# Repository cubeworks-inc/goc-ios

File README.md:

GOC Interface App for iOS
=========================

This app allows you to use your phone to send messages to M3 chips via the GOC
protocol using an iOS device.

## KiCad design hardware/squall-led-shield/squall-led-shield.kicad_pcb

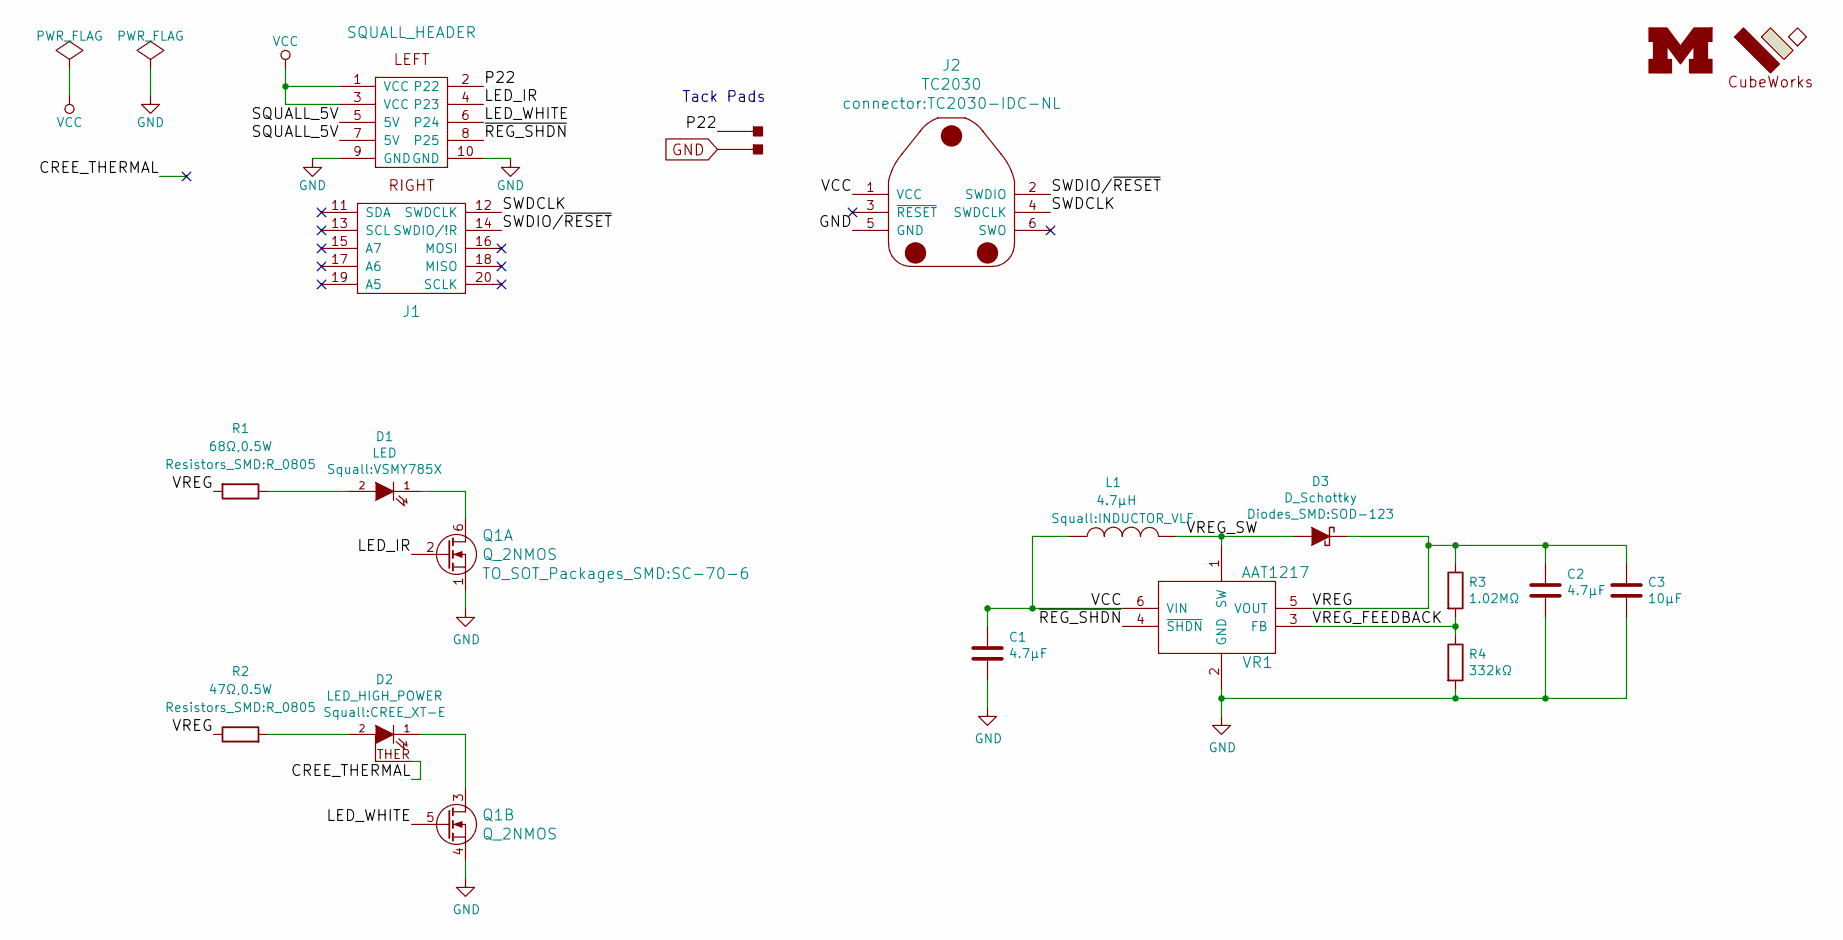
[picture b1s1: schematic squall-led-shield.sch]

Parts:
C1, C2: 4.7µF; C_0603
C3: 10µF; C_0603
D1: LED; VSMY785X
D2: LED_HIGH_POWER; CREE_XT-E
D3: D_Schottky; SOD-123
J1: SQUALL_HEADER
J2: TC2030; TC2030-IDC-NL
J3, J4: TACK_PAD; TACK_PAD_FB_75MIL
L1: 4.7µH; INDUCTOR_VLF
Q1: Q_2NMOS; SC-70-6
R1: 68Ω,0.5W; R_0805
R2: 47Ω,0.5W; R_0805
R3: 1.02MΩ; R_0603
R4: 332kΩ; R_0603
VR1: AAT1217; SOT-23-6
_1: CubeWorks-Logo; CubeWorks_Logo-5mm
_2: BLOCK_M; BLOCK_M_SOLID_100MIL

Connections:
/CREE_THERMAL: D2.THER (THERMAL)
/LED_IR: J1.4 (P23), Q1.2 (G1)
/LED_WHITE: J1.6 (P24), Q1.5 (G2)
/P22: J1.2 (P22), J3.1
/SQUALL_5V: J1.5 (5V), J1.7 (5V)
/SWDCLK: J1.12 (SWDCLK), J2.4 (SWDCLK)
/SWDIO/~RESET: J1.14 (SWDIO/!R), J2.2 (SWDIO)
/VREG: C2.1, C3.1, D3.1 (K), R1.2, R2.1, R3.1, VR1.5 (VOUT)
/VREG_FEEDBACK: R3.2, R4.1, VR1.3 (FB)
/VREG_SW: D3.2 (A), L1.2, VR1.1 (SW)
/~REG_SHDN: J1.8 (P25), VR1.4 (~SHDN)
GND: C1.2, C2.2, C3.2, J1.9 (GND), J1.10 (GND), J2.5 (GND), J4.1, Q1.1 (S1), Q1.4 (S1), R4.2, VR1.2 (GND)
unnamed: D1.1 (K), Q1.6 (D1)
unnamed: D1.2 (A), R1.1
unnamed: D2.1 (K), Q1.3 (D1)
unnamed: D2.2 (A), R2.2
VCC: C1.1, J1.1 (VCC), J1.3 (VCC), J2.1 (VCC), L1.1, VR1.6 (VIN)

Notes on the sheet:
Tack Pads

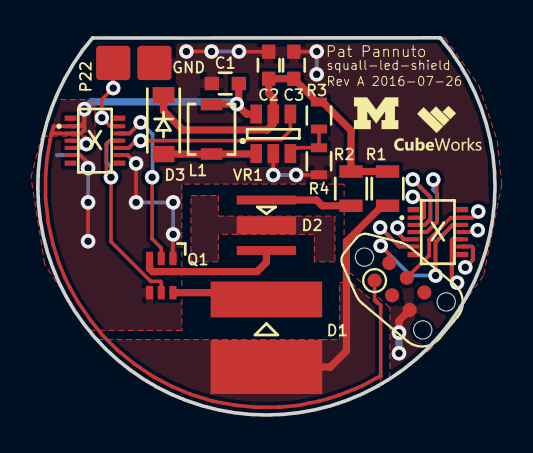
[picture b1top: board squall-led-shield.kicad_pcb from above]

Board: 2 copper layers, 25.4 x 21.0 mm, 19 parts (0 on the bottom side), 16 nets.

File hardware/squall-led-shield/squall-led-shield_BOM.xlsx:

Reference | Quantity | Value | Footprint | Datasheet | Description | Digikey | MFN | MFP
C1 C2 | 2 | 4.7µF | Capacitors_SMD:C_0603 |  |  | 490-3297-1-ND
C3 | 1 | 10µF | Capacitors_SMD:C_0603 |  |  | 490-3298-1-ND
D1 | 1 | LED | Squall:VSMY785X | http://www.vishay.com/docs/81145/vsmy7850.pdf | IR LED 850NM 1A | VSMY7850X01-GS08CT-ND | Vishay | VSMY7850X01-GS08
D2 | 1 | LED_HIGH_POWER | Squall:CREE_XT-E | http://www.cree.com/~/media/Files/Cree/LED%20Components%20an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 | LED XLAMP COOL WHITE 6200K 2SMD | XTEAWT-00-0000-000000G51CT-ND | ,
D3 | 1 | D_Schottky | Diodes_SMD:SOD-123 | http://www.onsemi.com/pub_link/Collateral/MBR0520LT1-D.PDF | DIODE SCHOTTKY 20V 500MA SOD123 | MBR0520LT1GOSCT-ND | ON Semiconductor | MBR0520LT1G
J1 | 1 | SQUALL_HEADER | Squall:SQUALL_HEADER |  | Header for a sensor board on top of the Squall BLE tag board. | H11617CT-ND | ,
L1 | 1 | 4.7µH | Squall:INDUCTOR_VLF | http://www.tdkkorea.co.kr/pro/down_pdf.php?No=75&real_file=1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 | 4.7µH Shielded Wirewound Inductor 740mA 190 mOhm Max Nonstandard | 445-3225-1-ND | TDK-Corporation | VLF3012AT-4R7MR74
Q1 | 1 | Q_2NMOS | TO_SOT_Packages_SMD:SC-70-6 | http://www.vishay.com/docs/67192/si1922ed.pdf | MOSFET 2N-CH 20V 1.3A SOT-363 | SI1922EDH-T1-GE3CT-ND | ,
R1 | 1 | 68Ω,0.5W | Resistors_SMD:R_0805 |  | RES SMD 68 OHM 5% 1/2W 0805 | P68ADCT-ND | ,
R2 | 1 | 47Ω,0.5W | Resistors_SMD:R_0805 |  | RES SMD 47 OHM 5% 1/2W 0805 | P47ADCT-ND | ,
R3 | 1 | 1.02MΩ | Resistors_SMD:R_0603 |  |  | 541-1.02MHCT-ND
R4 | 1 | 332kΩ | Resistors_SMD:R_0603 |  |  | 541-332KHCT-ND
VR1 | 1 | AAT1217 | TO_SOT_Packages_SMD:SOT-23-6 | http://www.skyworksinc.com/uploads/documents/AAT1217_202050B.pdf | Boost Switching Regulator IC Positive Adjustable 2.5V 1 Output 750mA (Switch) S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 | 863-1495-1-ND | Skyworks-Solutions-Inc. | AAT1217ICA-1.2-T1

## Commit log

2016-07-19 Initial UI
2016-07-21 Simple case GOC message generation working
2016-07-21 Add README
2016-07-21 Remove old attempts at UI interfacing
2016-07-21 Wire up GOC version; make GOCv1 work correctly
2016-07-21 Wire send buttons; fix validation logic
2016-07-21 Basic LED blinking code
    Not sure that iOS can support what we need :/, this gets a roughly
    40Hz strobe with maybe a 90% duty cycle. The Electric Imp BlinkUp
    protocol blinks the screen instead, getting a better balance, but
    they max out around 15 Hz, which given screen refresh rates isn't
    that surprising.
    Harumph.
2016-07-21 Move iPhone app into dedicated iOS folder
2016-07-21 Fix typo in userdefaults initializer
2016-07-24 WIP: Squall shield programming perhipheral
    This is my first time ever using KiCad, so likely rough.
2016-07-24 Put Squall headers on both sides of the board
2016-07-24 Not sure I agree that netlist file shouldn't be committed
2016-07-24 Add missing footprint for R2
2016-07-24 WIP: Place parts
2016-07-24 Fix pad names for CREE LED
2016-07-24 Hide `SQUALL_HEADER` value, ref
2016-07-24 Fix missing pin number on VR1
2016-07-24 WIP: Start routing
    KiCad does *not* seem okay with the current headers. Let's try to
    fix those by changing footprints
2016-07-24 WIP: Aha, routing issue was DRC-related
2016-07-24 WIP: Now I understand how pin mapping work
2016-07-24 WIP: Add explicit thermal pin
2016-07-24 WIP: Zones look better now...
2016-07-24 WIP: Okay, the router is cool once you get it
2016-07-24 WIP: Tie regulator to VCC
2016-07-24 Okay. That may be a board. Finally.
2016-07-24 Clean up silkscreen
2016-07-24 Add CubeWorks logo
2016-07-24 Draft for fab
2016-07-25 Fix squall header component
    I still don't totally understand what multi-component components
    are, but this header isn't one.
2016-07-25 WIP: Create proper nfet array component
    As I come to see enlightenment, I see that this is one where KiCad
    and Eagle both have it half right, but I think KiCad is closer to
    being able to be full right.
2016-07-25 WIP: Remove footer pads on bottom of squall header
2016-07-25 WIP: VREG -> 5V
2016-07-25 WIP: Fresh routing
2016-07-25 Clean up ground plane in top left
2016-07-26 Add Block M logo
2016-07-26 WIP: Add programming header
2016-07-26 WIP: Fix local version of header footprint
2016-07-26 Round VCC trace around the outside
2016-07-26 Add tack pads for last gpio
2016-07-26 Move fill around pad a bit
2016-07-26 Clean up fill around pad a bit
2016-07-27 Oops, save tack pad footprint in sch as well
2016-07-27 Fixup outline to touch
2016-07-27 Fix date
2016-07-27 Appease fill around gnd pad
2016-07-27 Add footprints for tack pads
2016-07-27 Update gerbers
2016-07-28 Add BOM
2017-07-06 initial firmware commit
2017-07-06 UART: intial uart code
2017-07-06 GOC: initial GOC code
2017-07-06 everything should be working, but it isn't
2017-07-06 FIRMWARE: reverted to sdk v11, now it seems to be working?
2017-07-06 UART: added timeout for bad commands
2017-07-07 GOC: now writes bytes LSB->MSB so no need to reverse the data
2017-07-07 MAIN: compiles out asserts for non-debug code
2017-12-29 Add installation and usage directions
2019-05-28 add support for `n' Manchester GOC
2019-07-25 make sure length field matches payload
2019-07-25 manchester goc is LSB not MSB
2019-07-25 don't flip bytes for new GOC
2019-07-25 active low
2019-08-14 push for speed and hope we get lucky
2019-08-14 document manual message
2019-09-06 don't do soft division in time-sensitive loop
